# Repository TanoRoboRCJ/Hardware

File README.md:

# Hardware

ロボットのハードウェアについてのリポジトリです。主に基板を扱います。

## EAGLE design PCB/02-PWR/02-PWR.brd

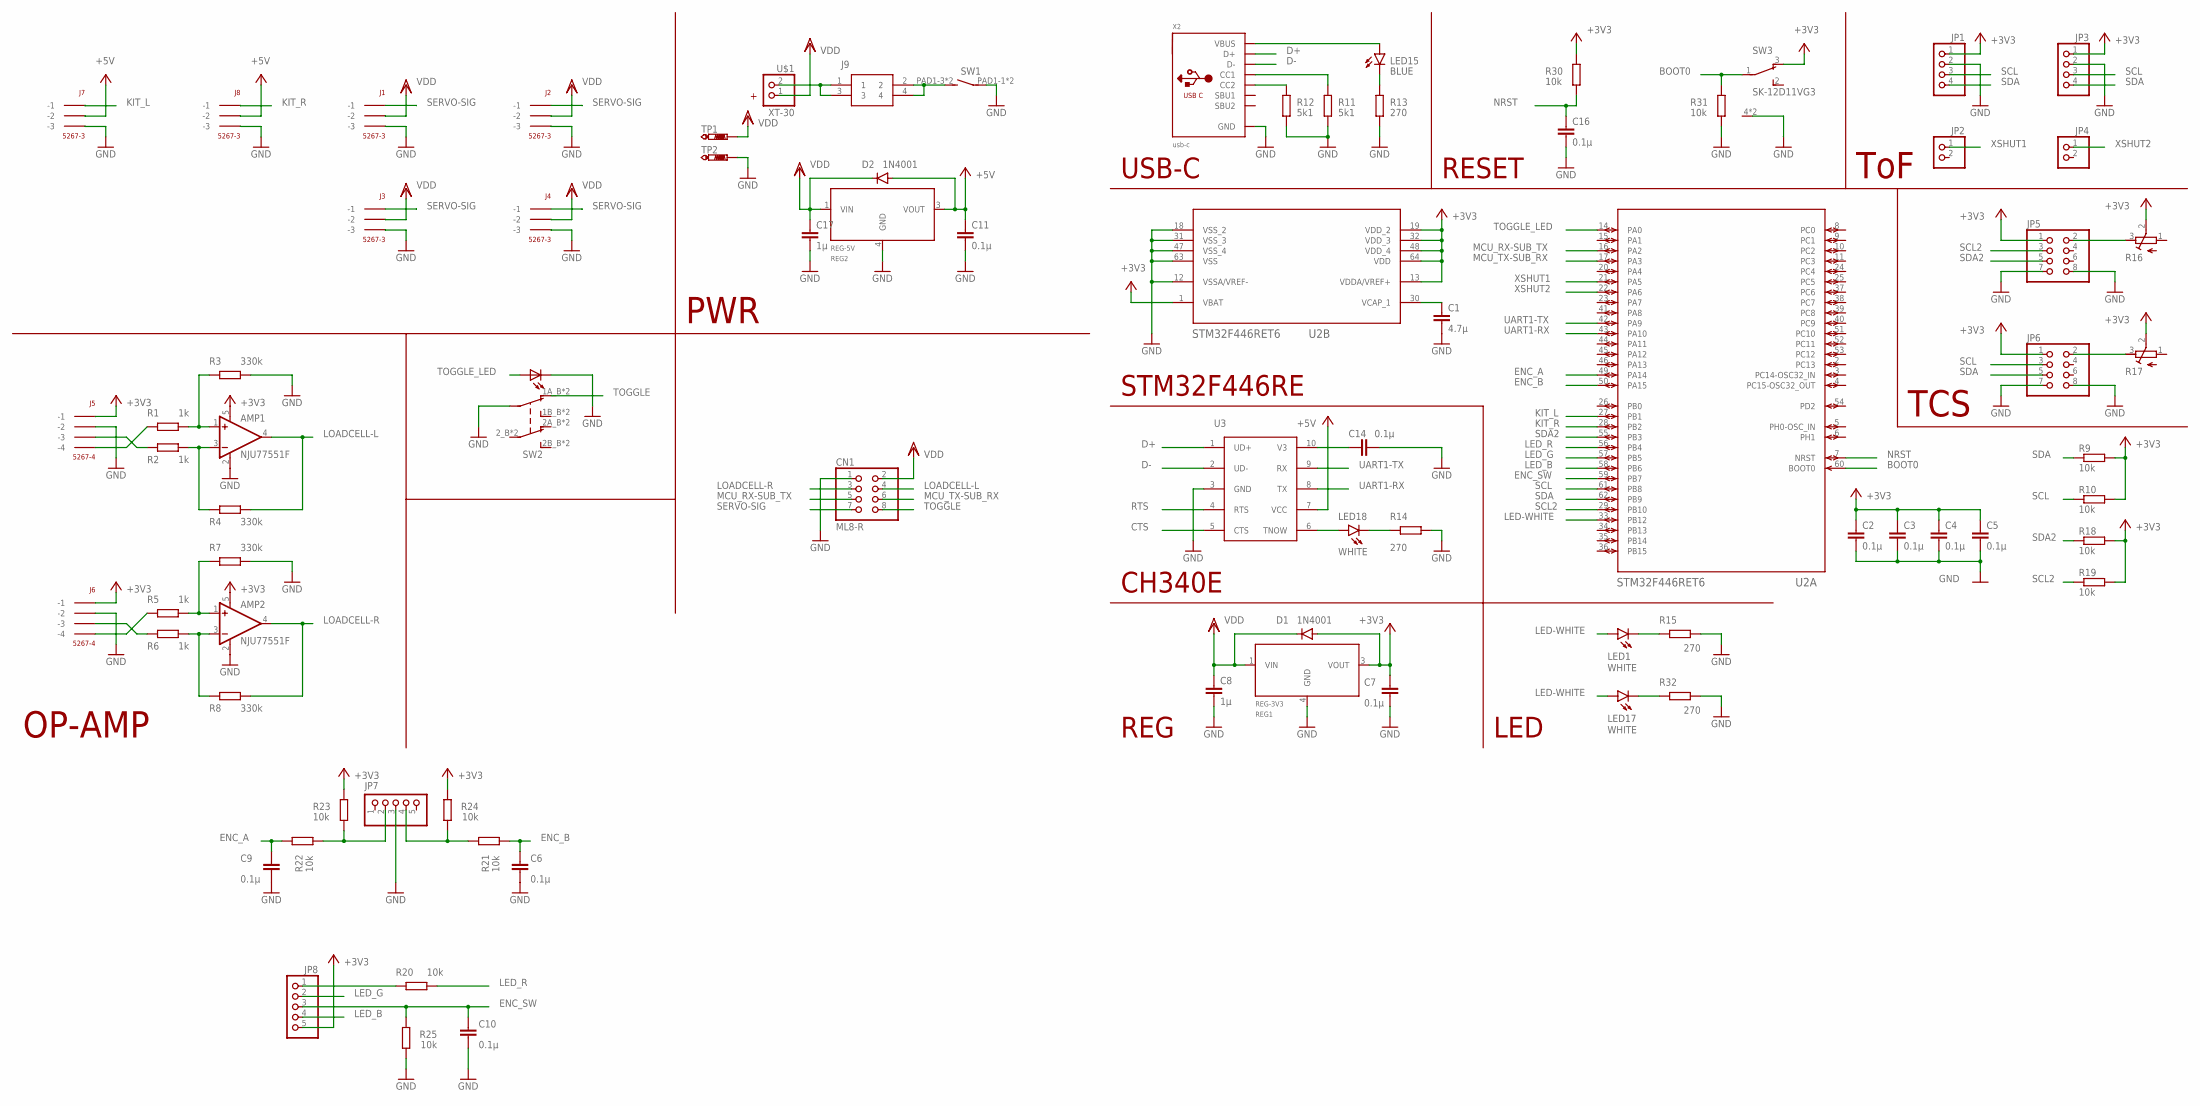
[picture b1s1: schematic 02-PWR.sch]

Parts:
AMP1, AMP2: NJU77551F; SOT23-5
C1: 4.7µ; C0603
C2, C3, C4, C5, C6, C7, C9, C10, C11, C14, C16: 0.1µ; C0603
C8, C17: 1µ; C0603
CN1: ML8-R; ML6
D1, D2: 1N4001; SMA-DO214AC
J1, J2, J3, J4, J7, J8: 5267-3
J5, J6: 5267-4
J9: 3557-2
JP1, JP3: PINHD-1X4; 1X04
JP2, JP4: PINHD-1X2; 1X02
JP5, JP6: PINHD-2X4; 2X04
JP7, JP8: PINHD-1X5; 1X05
LED1, LED17, LED18: WHITE; SML0603
LED15: BLUE; SML0603
R1, R2, R5, R6: 1k; R0805
R3, R4, R7, R8: 330k; R0805
R9, R10, R18, R19, R20, R21, R22, R23, R24, R25, R30, R31: 10k; R0402
R11, R12: 5k1; R0402
R13, R14, R15, R32: 270; R0402
R16, R17: R-TRIMM3339P; RTRIM3339P
REG1: REG-3V3; MYPARTS_D-PAK_TO252AA
REG2: REG-5V; MYPARTS_D-PAK_TO252AA
SW1: MYPARTS2_C01B02BKBK-EI
SW2: TL22
SW3: SK-12D11VG3
TP1, TP2: PTR1TP16R; TP16R
U2: STM32F446RET6; LQFP64-10X10MM
U3: CH340ESMD; MSOP10
U$1: XT-30
X2: usb-c; USB_C_CUSB31-CFM2AX-01-X

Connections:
+3V3: AMP1.5 (V+), AMP2.5 (V+), C2.1, C3.1, C4.1, C5.1, C7.1, D1.A, J5.P$1 (-1), J6.P$1 (-1), JP1.1, JP3.1, JP5.1, JP6.1, JP8.5, R9.2, R10.2, R16.2 (S), R17.2 (S), R18.2, R19.2, R23.1, R24.1, R30.1, REG1.3 (VOUT), SW3.3 (O), U2.1 (VBAT), U2.13 (VDDA/VREF+), U2.19 (VDD_2), U2.32 (VDD_3), U2.48 (VDD_4), U2.64 (VDD)
+5V: C11.1, D2.A, J7.P$2 (-2), J8.P$2 (-2), REG2.3 (VOUT), U3.7 (VCC)
BOOT0: R31.1, SW3.1, U2.60 (BOOT0)
CTS: U3.5 (CTS)
D+: U3.1 (UD+), X2.A6 (D+), X2.B6 (D+)
D-: U3.2 (UD-), X2.A7 (D-), X2.B7 (D-)
ENC_A: C9.1, R22.1, U2.49 (PA14)
ENC_B: C6.1, R21.2, U2.50 (PA15)
ENC_SW: C10.1, JP8.3, R25.1, U2.59 (PB7)
GND: AMP1.2 (V-), AMP2.2 (V-), C1.2, C2.2, C3.2, C4.2, C5.2, C6.2, C7.2, C8.2, C9.2, C10.2, C11.2, C14.2, C16.2, C17.2, CN1.1, J1.P$3 (-3), J2.P$3 (-3), J3.P$3 (-3), J4.P$3 (-3), J5.P$2 (-2), J6.P$2 (-2), J7.P$3 (-3), J8.P$3 (-3), JP1.2, JP3.2, JP5.7, JP5.8, JP6.7, JP6.8, JP7.3, R3.2, R7.2, R11.2, R12.2, R13.1, R14.1, R15.1, R25.2, R31.2, R32.1, REG1.4 (GND), REG2.4 (GND), SW1.PAD1-1, SW1.PAD1-2, SW2.1_B (1), SW2.1_T (1), SW2.L-_B (C), SW2.L-_T (C), SW3.4 (CASE), SW3.5 (CASE), TP2.TP, U2.12 (VSSA/VREF-), U2.18 (VSS_2), U2.31 (VSS_3), U2.47 (VSS_4), U2.63 (VSS), U3.3 (GND), X2.A1B12 (GND), X2.B1A12 (GND)
KIT_L: J7.P$1 (-1), U2.27 (PB1)
KIT_R: J8.P$1 (-1), U2.28 (PB2)
LED-WHITE: LED1.A, LED17.A, U2.33 (PB12)
LED_B: JP8.4, U2.58 (PB6)
LED_G: JP8.2, U2.57 (PB5)
LED_R: R20.2, U2.56 (PB4)
LOADCELL-L: AMP1.4 (OUT), CN1.4, R4.2
LOADCELL-R: AMP2.4 (OUT), CN1.3, R8.2
MCU_RX-SUB_TX: CN1.5, U2.16 (PA2)
MCU_TX-SUB_RX: CN1.6, U2.17 (PA3)
unnamed: J5.P$3 (-3), R2.1
unnamed: J5.P$4 (-4), R1.1
unnamed: AMP1.3 (-IN), R2.2, R4.1
unnamed: AMP1.1 (+IN), R1.2, R3.1
unnamed: J6.P$3 (-3), R6.1
unnamed: J6.P$4 (-4), R5.1
unnamed: AMP2.3 (-IN), R6.2, R8.1
unnamed: AMP2.1 (+IN), R5.2, R7.1
unnamed: J9.1, J9.3, U$1.2
unnamed: J9.2, J9.4, SW1.PAD1-3 (S), SW1.PAD1-4 (S)
unnamed: C14.1, U3.10 (V3)
unnamed: LED1.C, R15.2
unnamed: JP5.2, R16.3 (E)
unnamed: R11.1, X2.A5 (CC1)
unnamed: R12.1, X2.B5 (CC2)
unnamed: LED15.C, R13.2
unnamed: JP6.2, R17.3 (E)
unnamed: C1.1, U2.30 (VCAP_1)
unnamed: LED18.A, U3.6 (TNOW)
unnamed: LED18.C, R14.2
unnamed: JP7.4, R21.1, R24.2
unnamed: JP7.2, R22.2, R23.2
unnamed: JP8.1, R20.1
unnamed: LED17.C, R32.2
unnamed: LED15.A, X2.A4B9 (VBUS), X2.B4A9 (VBUS)
NRST: C16.1, R30.2, U2.7 (NRST)
RTS: U3.4 (RTS)
SCL: JP1.3, JP3.3, JP6.3, R10.1, U2.61 (PB8)
SCL2: JP5.3, R19.1, U2.29 (PB10)
SDA: JP1.4, JP3.4, JP6.5, R9.1, U2.62 (PB9)
SDA2: JP5.5, R18.1, U2.55 (PB3)
SERVO-SIG: CN1.7, J1.P$1 (-1), J2.P$1 (-1), J3.P$1 (-1), J4.P$1 (-1)
TOGGLE: CN1.8, SW2.1A_B (1A), SW2.1A_T (1A)
TOGGLE_LED: SW2.L+_B (A), SW2.L+_T (A), U2.14 (PA0)
UART1-RX: U2.43 (PA10), U3.8 (TX)
UART1-TX: U2.42 (PA9), U3.9 (RX)
VDD: C8.1, C17.1, CN1.2, D1.K (C), D2.K (C), J1.P$2 (-2), J2.P$2 (-2), J3.P$2 (-2), J4.P$2 (-2), REG1.1 (VIN), REG2.1 (VIN), TP1.TP, U$1.1
XSHUT1: JP2.1, U2.21 (PA5)
XSHUT2: JP4.1, U2.22 (PA6)

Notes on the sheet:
PWR
ToF
OP-AMP
STM32F446RE
REG
CH340E
USB-C
RESET
LED
TCS

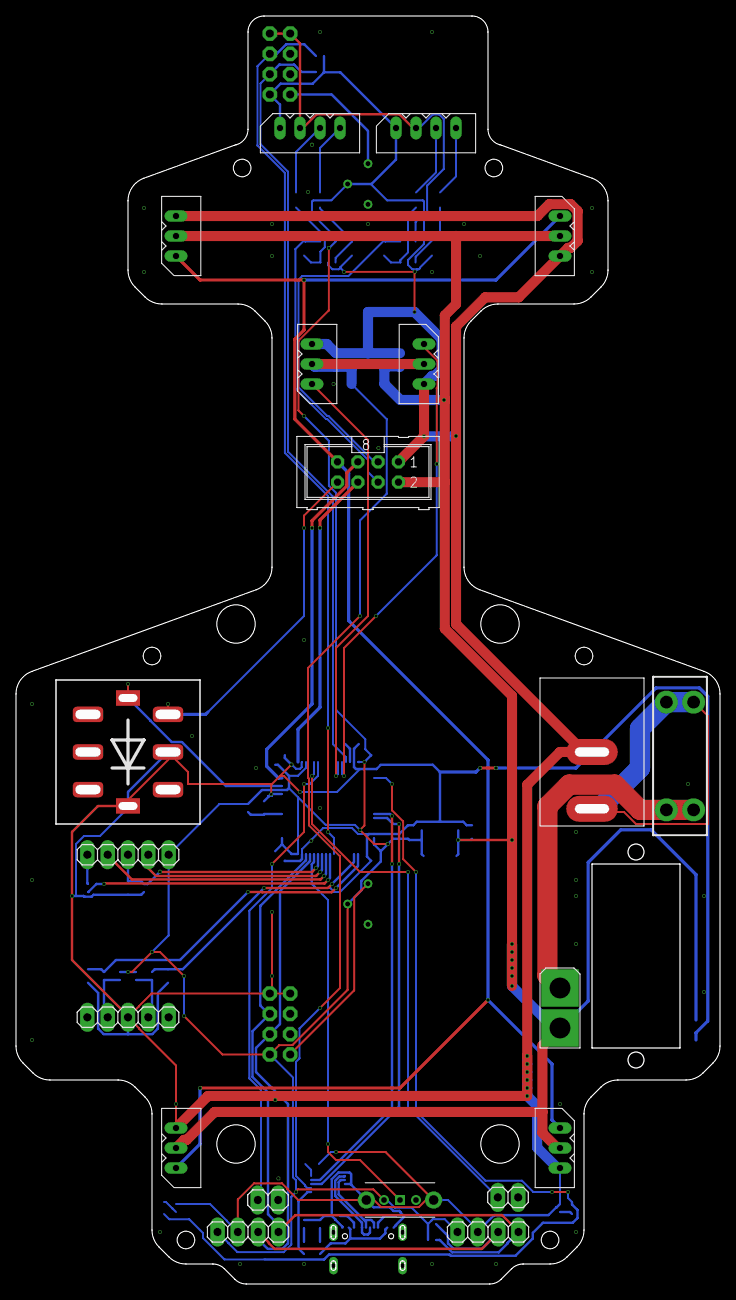
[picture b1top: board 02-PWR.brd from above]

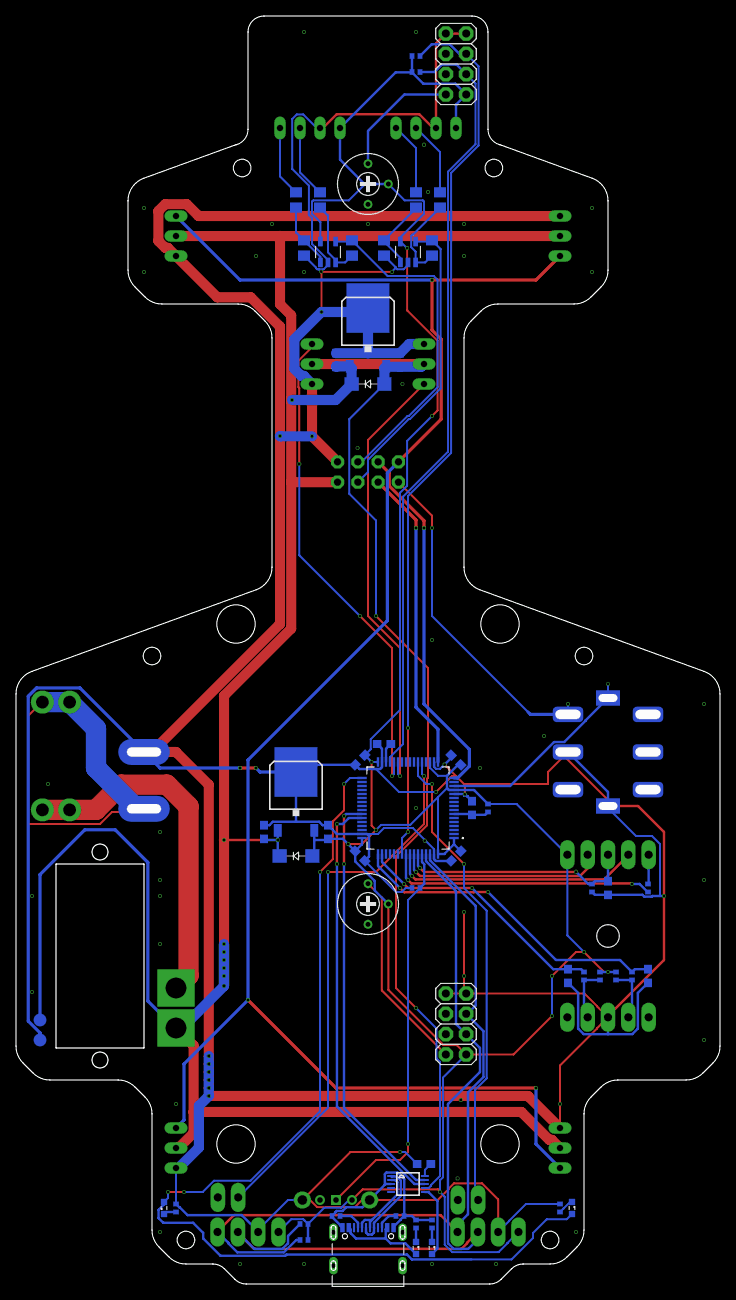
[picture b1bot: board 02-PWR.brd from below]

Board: 2 copper layers, 88.0 x 158.5 mm, 79 parts (59 on the bottom side), 57 nets.

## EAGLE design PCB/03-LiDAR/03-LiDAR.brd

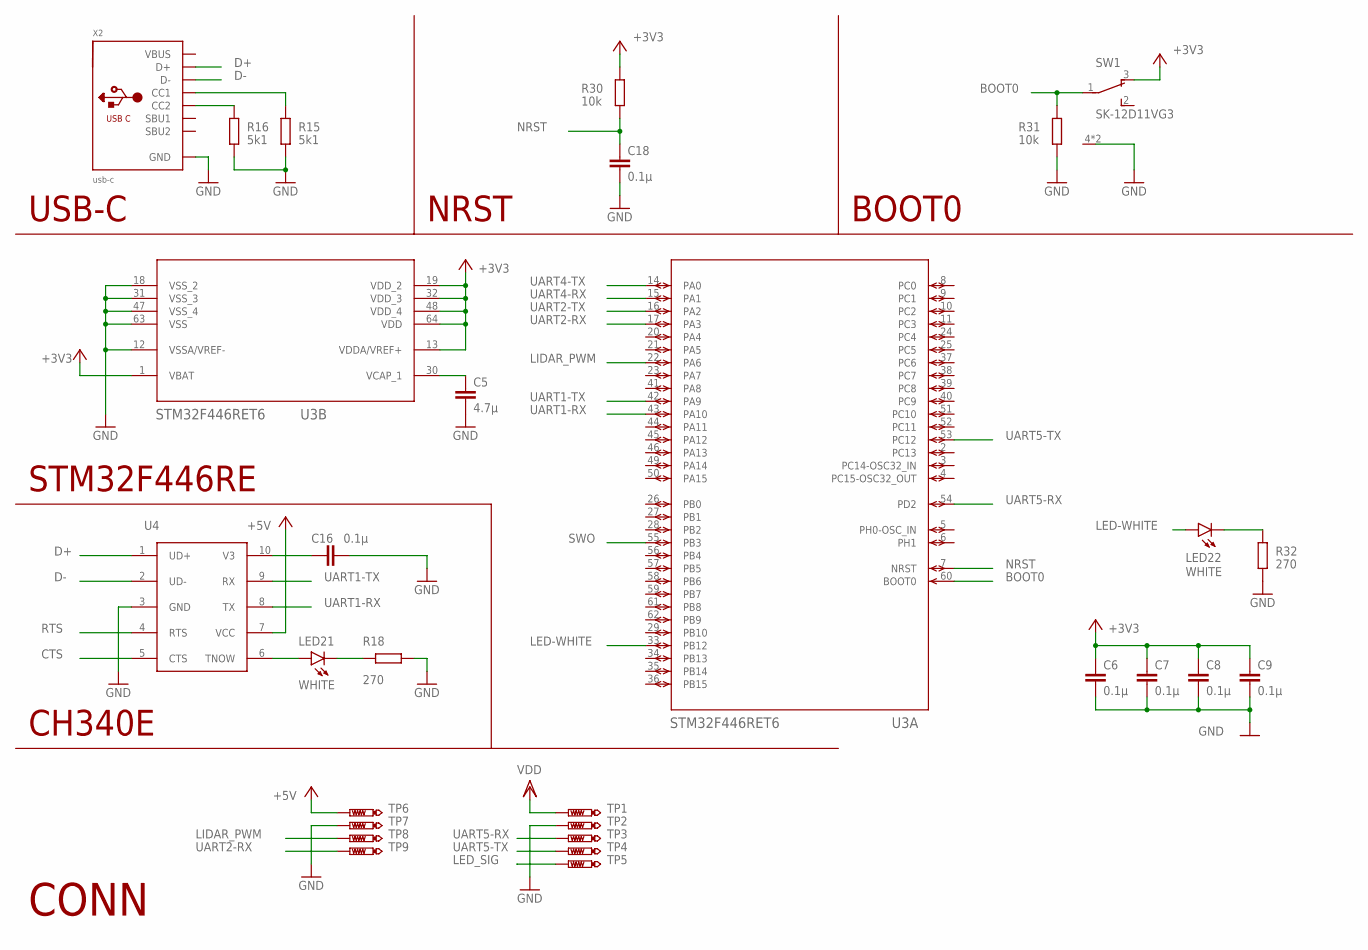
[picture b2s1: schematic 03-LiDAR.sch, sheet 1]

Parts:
C5: 4.7µ; C0603
C6, C7, C8, C9, C16, C18: 0.1µ; C0603
LED21, LED22: WHITE; SML0603
R15, R16: 5k1; R0402
R18, R32: 270; R0402
R30, R31: 10k; R0402
SW1: SK-12D11VG3
TP1, TP3, TP4, TP5, TP6, TP8, TP9: PTR1TP10R; TP10R
TP2, TP7: PTR1TP10SQ; TP10SQ
U3: STM32F446RET6; LQFP64-10X10MM
U4: CH340ESMD; MSOP10
X2: usb-c; USB_C_CUSB31-CFM2AX-01-X

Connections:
+3V3: C6.1, C7.1, C8.1, C9.1, R30.1, SW1.3 (O), U3.1 (VBAT), U3.13 (VDDA/VREF+), U3.19 (VDD_2), U3.32 (VDD_3), U3.48 (VDD_4), U3.64 (VDD); also elsewhere on the board
+5V: TP6.TP, U4.7 (VCC); also elsewhere on the board
BOOT0: R31.1, SW1.1, U3.60 (BOOT0)
CTS: U4.5 (CTS)
D+: U4.1 (UD+), X2.A6 (D+), X2.B6 (D+)
D-: U4.2 (UD-), X2.A7 (D-), X2.B7 (D-)
GND: C5.2, C6.2, C7.2, C8.2, C9.2, C16.2, C18.2, R15.2, R16.2, R18.1, R31.2, R32.1, SW1.4 (CASE), SW1.5 (CASE), TP2.TP, TP7.TP, U3.12 (VSSA/VREF-), U3.18 (VSS_2), U3.31 (VSS_3), U3.47 (VSS_4), U3.63 (VSS), U4.3 (GND), X2.A1B12 (GND), X2.B1A12 (GND); also elsewhere on the board
LED-WHITE: LED22.A, U3.33 (PB12)
LED_SIG: TP5.TP; also elsewhere on the board
LIDAR_PWM: TP8.TP, U3.22 (PA6)
unnamed: R15.1, X2.A5 (CC1)
unnamed: R16.1, X2.B5 (CC2)
unnamed: C5.1, U3.30 (VCAP_1)
unnamed: C16.1, U4.10 (V3)
unnamed: LED21.A, U4.6 (TNOW)
unnamed: LED21.C, R18.2
unnamed: LED22.C, R32.2
NRST: C18.1, R30.2, U3.7 (NRST)
RTS: U4.4 (RTS)
SWO: U3.55 (PB3)
UART1-RX: U3.43 (PA10), U4.8 (TX)
UART1-TX: U3.42 (PA9), U4.9 (RX)
UART2-RX: TP9.TP, U3.17 (PA3)
UART2-TX: U3.16 (PA2)
UART4-RX: U3.15 (PA1); also elsewhere on the board
UART4-TX: U3.14 (PA0)
UART5-RX: TP3.TP, U3.54 (PD2); also elsewhere on the board
UART5-TX: TP4.TP, U3.53 (PC12)
VBUS: X2.A4B9 (VBUS), X2.B4A9 (VBUS)
VDD: TP1.TP; also elsewhere on the board

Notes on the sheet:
CONN
STM32F446RE
CH340E
USB-C
BOOT0
NRST

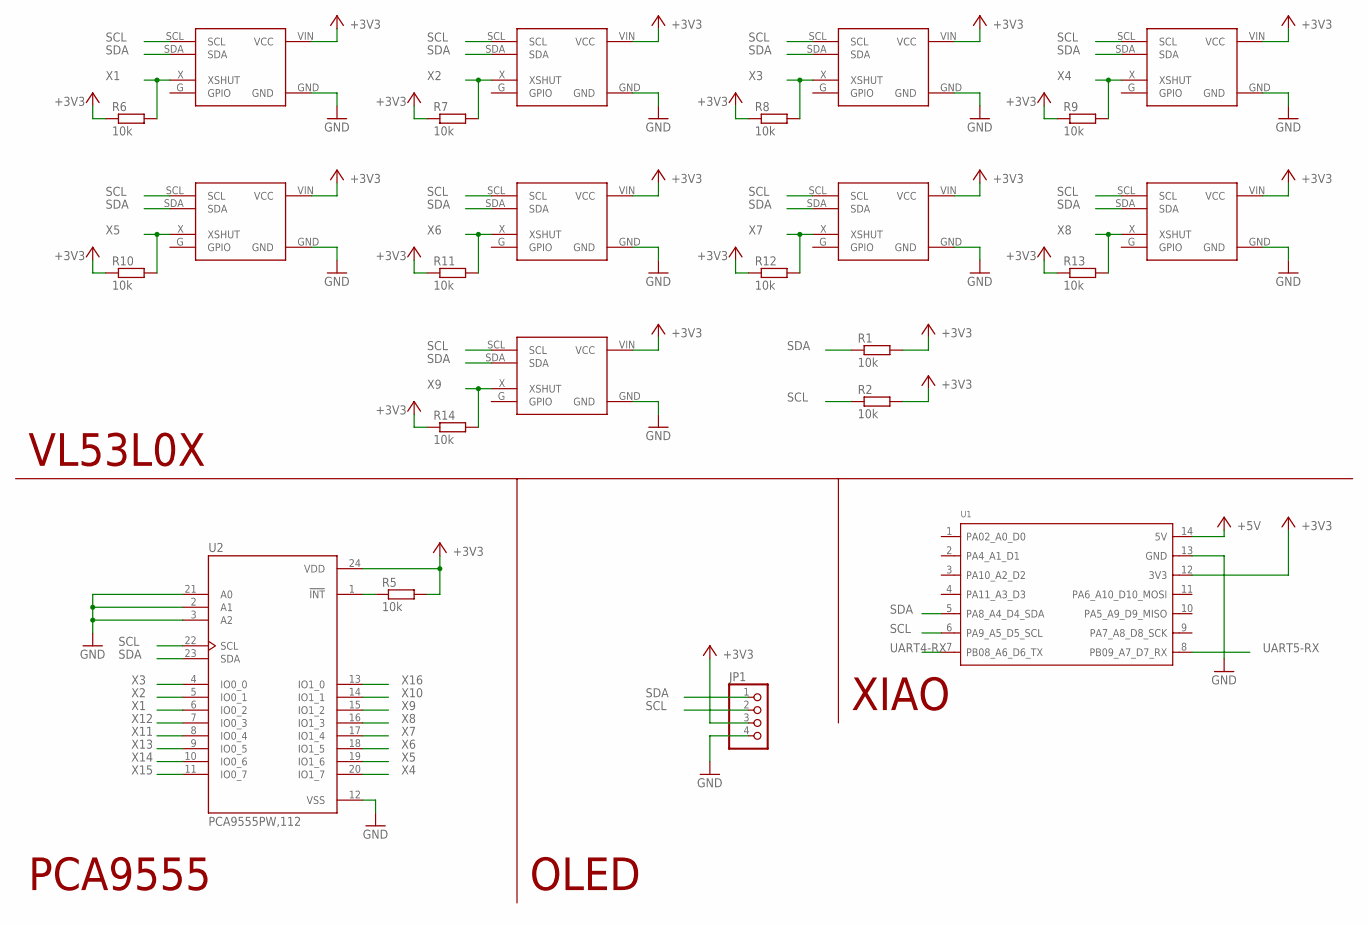
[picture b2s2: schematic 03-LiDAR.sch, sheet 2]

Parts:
JP1: PINHD-1X4; 1X04
R1, R2, R5, R6, R7, R8, R9, R10, R11, R12, R13, R14: 10k; R0402
U1: MOUDLE-SEEEDUINO-XIAO; MOUDLE14P-2.54-21X17.8MM
U2: PCA9555PW,112; SOP65P640X110-24N
VL1, VL2, VL3, VL4, VL5, VL6, VL7, VL8, VL9: VL53L0X; 1X04

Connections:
+3V3: JP1.3, R1.2, R2.2, R5.2, R6.1, R7.1, R8.1, R9.1, R10.1, R11.1, R12.1, R13.1, R14.1, U1.12 (3V3), U2.24 (VDD), VL1.VIN (VCC), VL2.VIN (VCC), VL3.VIN (VCC), VL4.VIN (VCC), VL5.VIN (VCC), VL6.VIN (VCC), VL7.VIN (VCC), VL8.VIN (VCC), VL9.VIN (VCC); also elsewhere on the board
+5V: U1.14 (5V); also elsewhere on the board
GND: JP1.4, U1.13 (GND), U2.2 (A1), U2.3 (A2), U2.12 (VSS), U2.21 (A0), VL1.GND, VL2.GND, VL3.GND, VL4.GND, VL5.GND, VL6.GND, VL7.GND, VL8.GND, VL9.GND; also elsewhere on the board
unnamed: R5.1, U2.1 (!INT)
SCL: JP1.2, R2.1, U1.6 (PA9_A5_D5_SCL), U2.22 (SCL), VL1.SCL, VL2.SCL, VL3.SCL, VL4.SCL, VL5.SCL, VL6.SCL, VL7.SCL, VL8.SCL, VL9.SCL
SDA: JP1.1, R1.1, U1.5 (PA8_A4_D4_SDA), U2.23 (SDA), VL1.SDA, VL2.SDA, VL3.SDA, VL4.SDA, VL5.SDA, VL6.SDA, VL7.SDA, VL8.SDA, VL9.SDA
UART4-RX: U1.7 (PB08_A6_D6_TX); also elsewhere on the board
UART5-RX: U1.8 (PB09_A7_D7_RX); also elsewhere on the board
X1: R6.2, U2.6 (IO0_2), VL1.X (XSHUT)
X2: R7.2, U2.5 (IO0_1), VL2.X (XSHUT)
X3: R8.2, U2.4 (IO0_0), VL3.X (XSHUT)
X4: R9.2, U2.20 (IO1_7), VL4.X (XSHUT)
X5: R10.2, U2.19 (IO1_6), VL5.X (XSHUT)
X6: R11.2, U2.18 (IO1_5), VL6.X (XSHUT)
X7: R12.2, U2.17 (IO1_4), VL7.X (XSHUT)
X8: R13.2, U2.16 (IO1_3), VL8.X (XSHUT)
X9: R14.2, U2.15 (IO1_2), VL9.X (XSHUT)
X10: U2.14 (IO1_1)
X11: U2.8 (IO0_4)
X12: U2.7 (IO0_3)
X13: U2.9 (IO0_5)
X14: U2.10 (IO0_6)
X15: U2.11 (IO0_7)
X16: U2.13 (IO1_0)

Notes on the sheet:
VL53L0X
XIAO
PCA9555
OLED

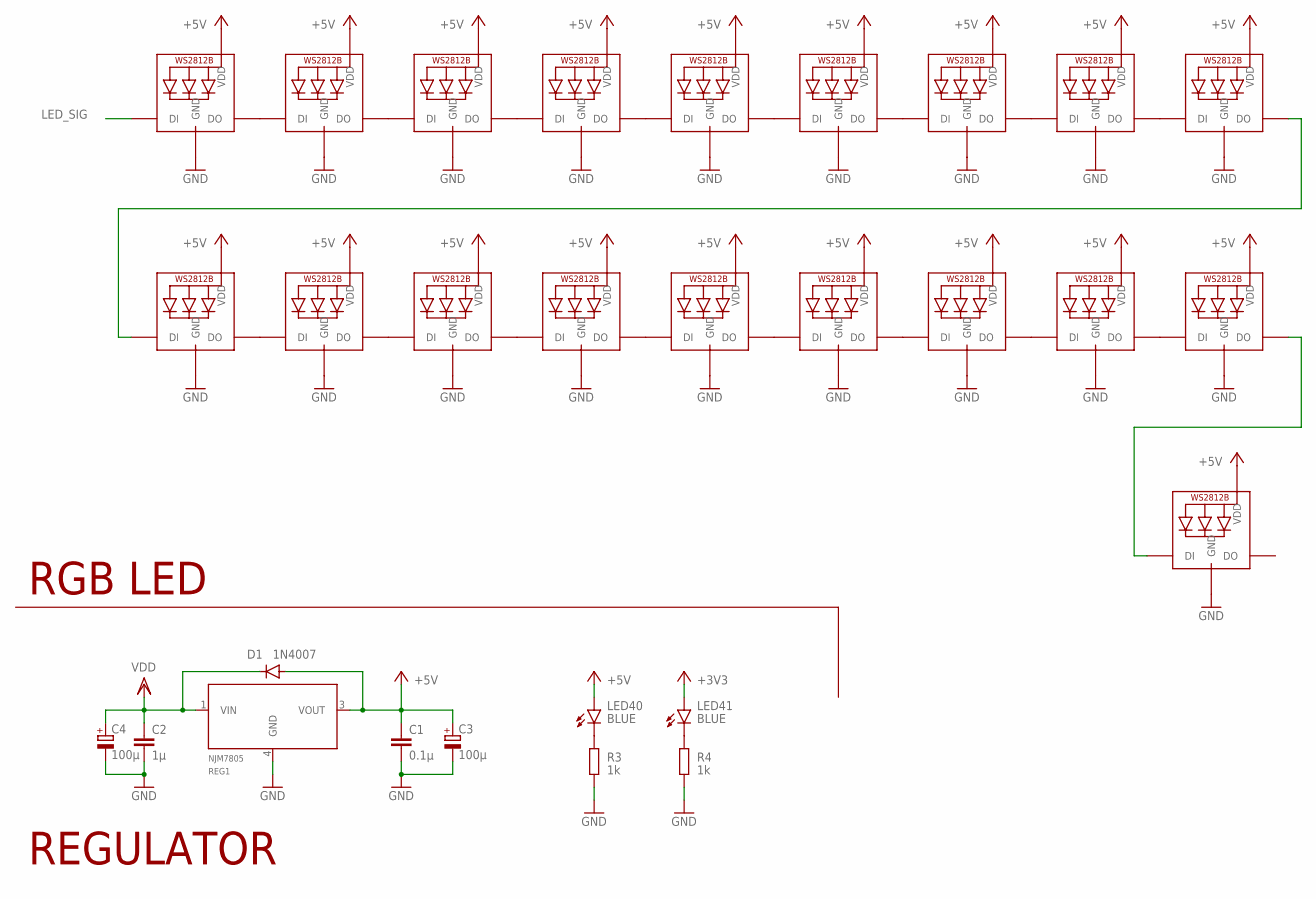
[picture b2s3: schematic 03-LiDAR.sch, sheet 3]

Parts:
C1: 0.1μ; C0402
C2: 1μ; C0402
C3, C4: 100μ; 153CLV-0505
D1: 1N4007; SMA-DO214AC
LED1, LED2, LED3, LED4, LED5, LED6, LED7, LED8, LED9, LED10, LED11, LED12, LED13, LED14, LED15, LED16, LED17, LED18, LED19: WS2812B_5050N; WS2812B-NARROW
LED40, LED41: BLUE; SML0603
R3, R4: 1k; R0402
REG1: NJM7805; MYPARTS_D-PAK_TO252AA

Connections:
+3V3: LED41.A; also elsewhere on the board
+5V: C1.1, C3.+, D1.A, LED1.1-VDD (VDD), LED2.1-VDD (VDD), LED3.1-VDD (VDD), LED4.1-VDD (VDD), LED5.1-VDD (VDD), LED6.1-VDD (VDD), LED7.1-VDD (VDD), LED8.1-VDD (VDD), LED9.1-VDD (VDD), LED10.1-VDD (VDD), LED11.1-VDD (VDD), LED12.1-VDD (VDD), LED13.1-VDD (VDD), LED14.1-VDD (VDD), LED15.1-VDD (VDD), LED16.1-VDD (VDD), LED17.1-VDD (VDD), LED18.1-VDD (VDD), LED19.1-VDD (VDD), LED40.A, REG1.3 (VOUT); also elsewhere on the board
GND: C1.2, C2.2, C3.-, C4.-, LED1.3-GND (GND), LED2.3-GND (GND), LED3.3-GND (GND), LED4.3-GND (GND), LED5.3-GND (GND), LED6.3-GND (GND), LED7.3-GND (GND), LED8.3-GND (GND), LED9.3-GND (GND), LED10.3-GND (GND), LED11.3-GND (GND), LED12.3-GND (GND), LED13.3-GND (GND), LED14.3-GND (GND), LED15.3-GND (GND), LED16.3-GND (GND), LED17.3-GND (GND), LED18.3-GND (GND), LED19.3-GND (GND), R3.2, R4.2, REG1.4 (GND); also elsewhere on the board
LED_SIG: LED1.4-DIN (DI); also elsewhere on the board
unnamed: LED1.2-DOUT (DO), LED2.4-DIN (DI)
unnamed: LED2.2-DOUT (DO), LED3.4-DIN (DI)
unnamed: LED3.2-DOUT (DO), LED4.4-DIN (DI)
unnamed: LED4.2-DOUT (DO), LED5.4-DIN (DI)
unnamed: LED5.2-DOUT (DO), LED6.4-DIN (DI)
unnamed: LED6.2-DOUT (DO), LED7.4-DIN (DI)
unnamed: LED7.2-DOUT (DO), LED8.4-DIN (DI)
unnamed: LED8.2-DOUT (DO), LED9.4-DIN (DI)
unnamed: LED10.2-DOUT (DO), LED11.4-DIN (DI)
unnamed: LED11.2-DOUT (DO), LED12.4-DIN (DI)
unnamed: LED12.2-DOUT (DO), LED13.4-DIN (DI)
unnamed: LED13.2-DOUT (DO), LED14.4-DIN (DI)
unnamed: LED14.2-DOUT (DO), LED15.4-DIN (DI)
unnamed: LED15.2-DOUT (DO), LED16.4-DIN (DI)
unnamed: LED16.2-DOUT (DO), LED17.4-DIN (DI)
unnamed: LED17.2-DOUT (DO), LED18.4-DIN (DI)
unnamed: LED40.C, R3.1
unnamed: LED41.C, R4.1
unnamed: LED9.2-DOUT (DO), LED10.4-DIN (DI)
unnamed: LED18.2-DOUT (DO), LED19.4-DIN (DI)
VDD: C2.1, C4.+, D1.K (C), REG1.1 (VIN); also elsewhere on the board

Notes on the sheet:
REGULATOR
RGB LED

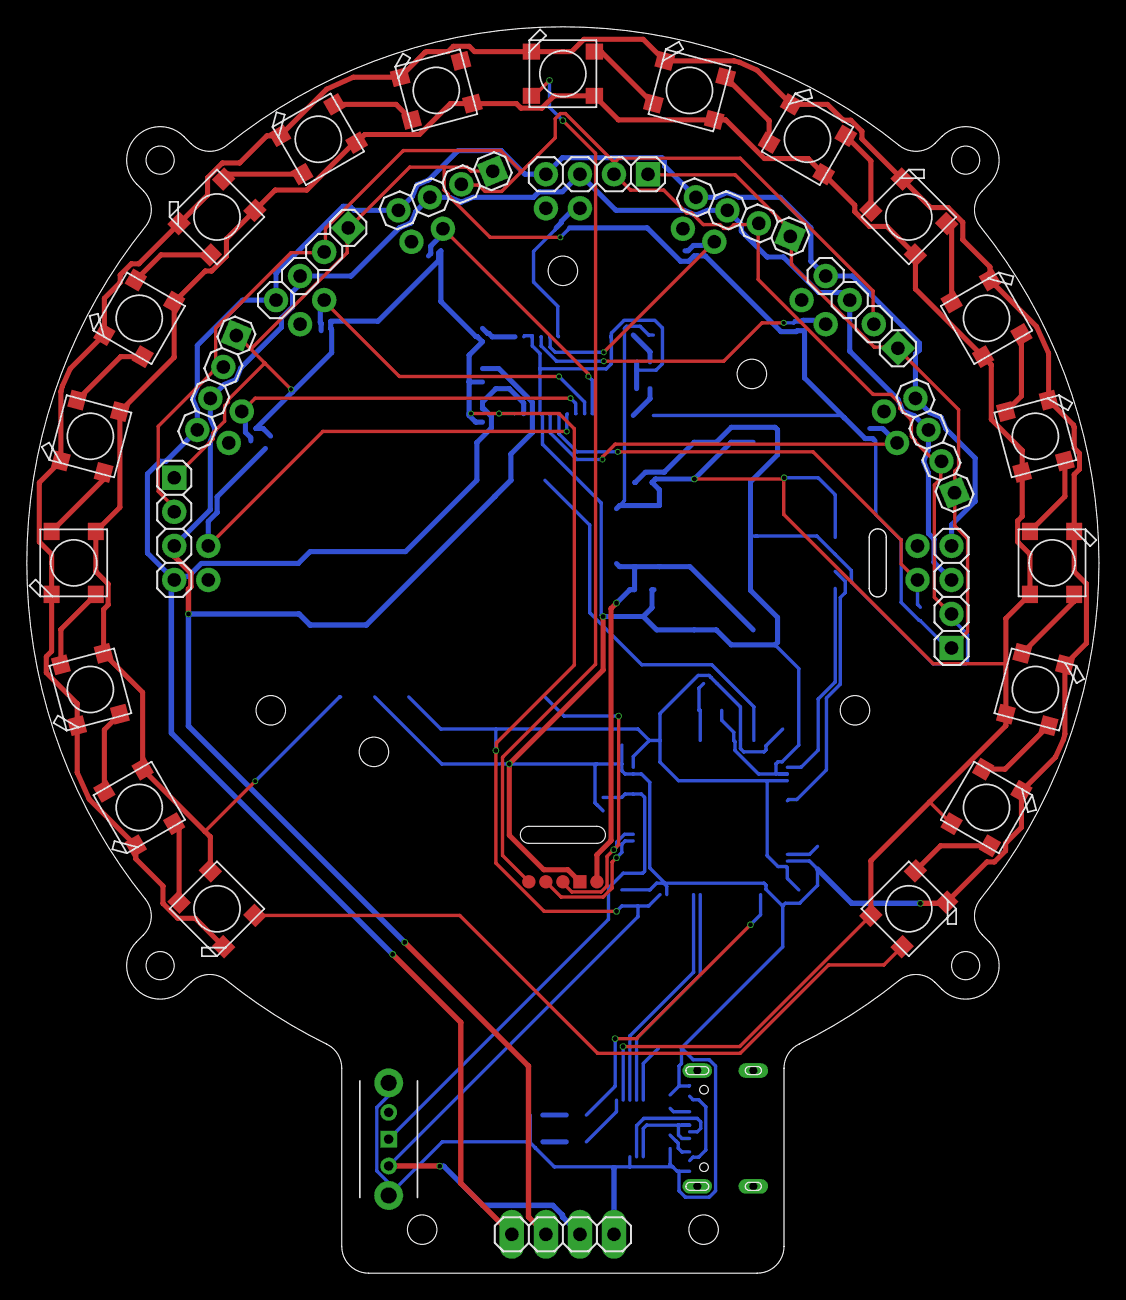
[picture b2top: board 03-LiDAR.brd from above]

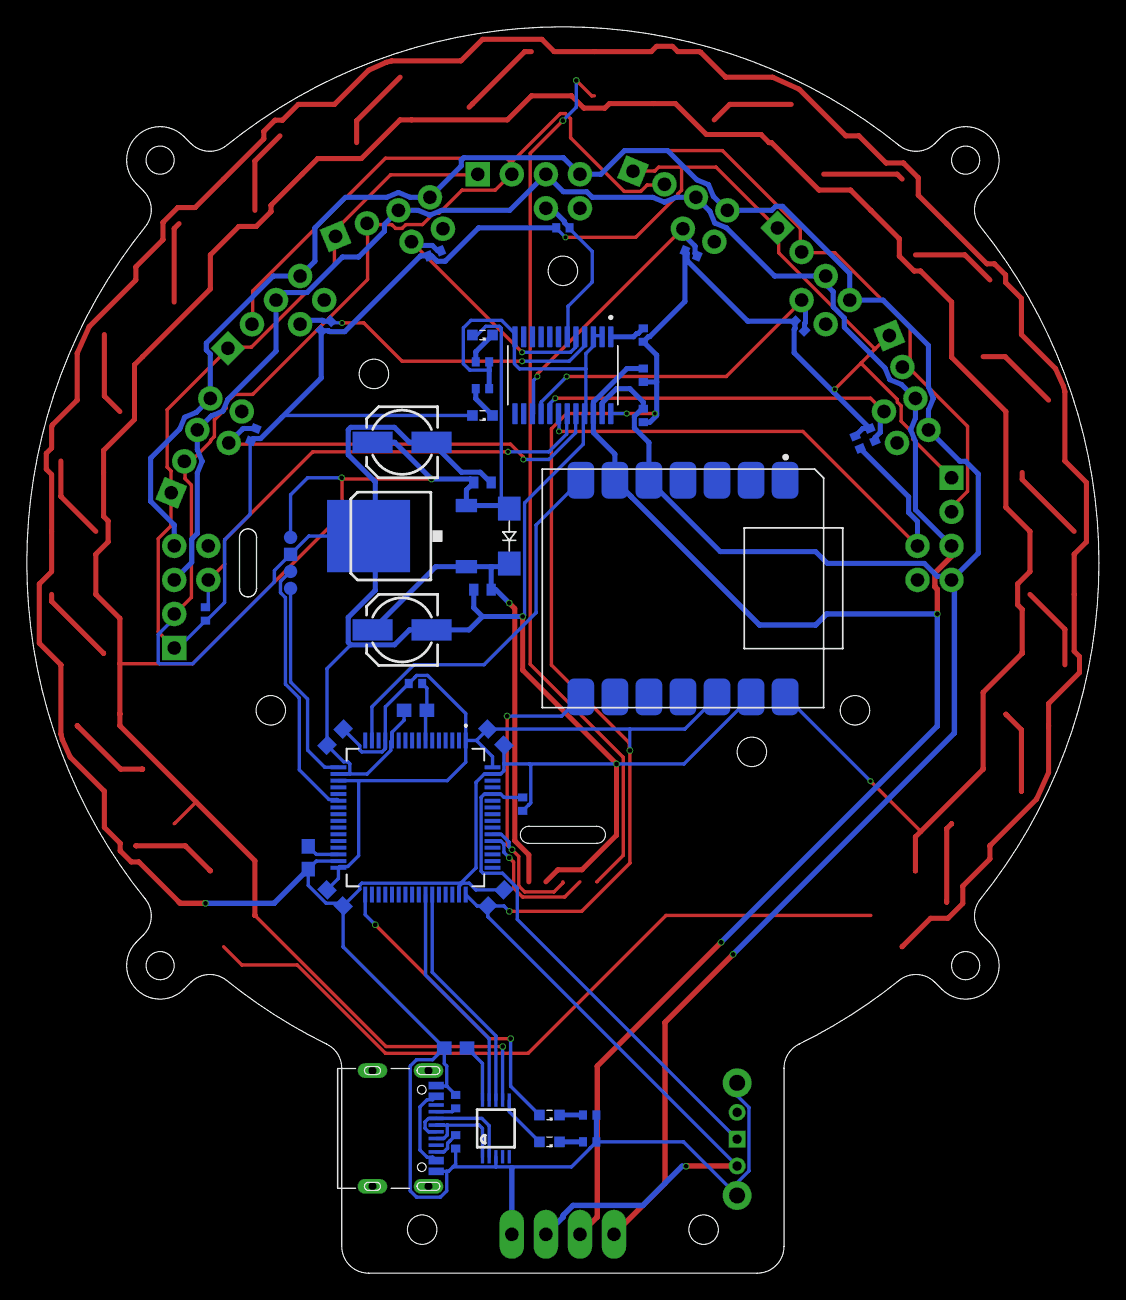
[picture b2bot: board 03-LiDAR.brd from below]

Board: 2 copper layers, 80.0 x 93.0 mm, 81 parts (46 on the bottom side), 57 nets.

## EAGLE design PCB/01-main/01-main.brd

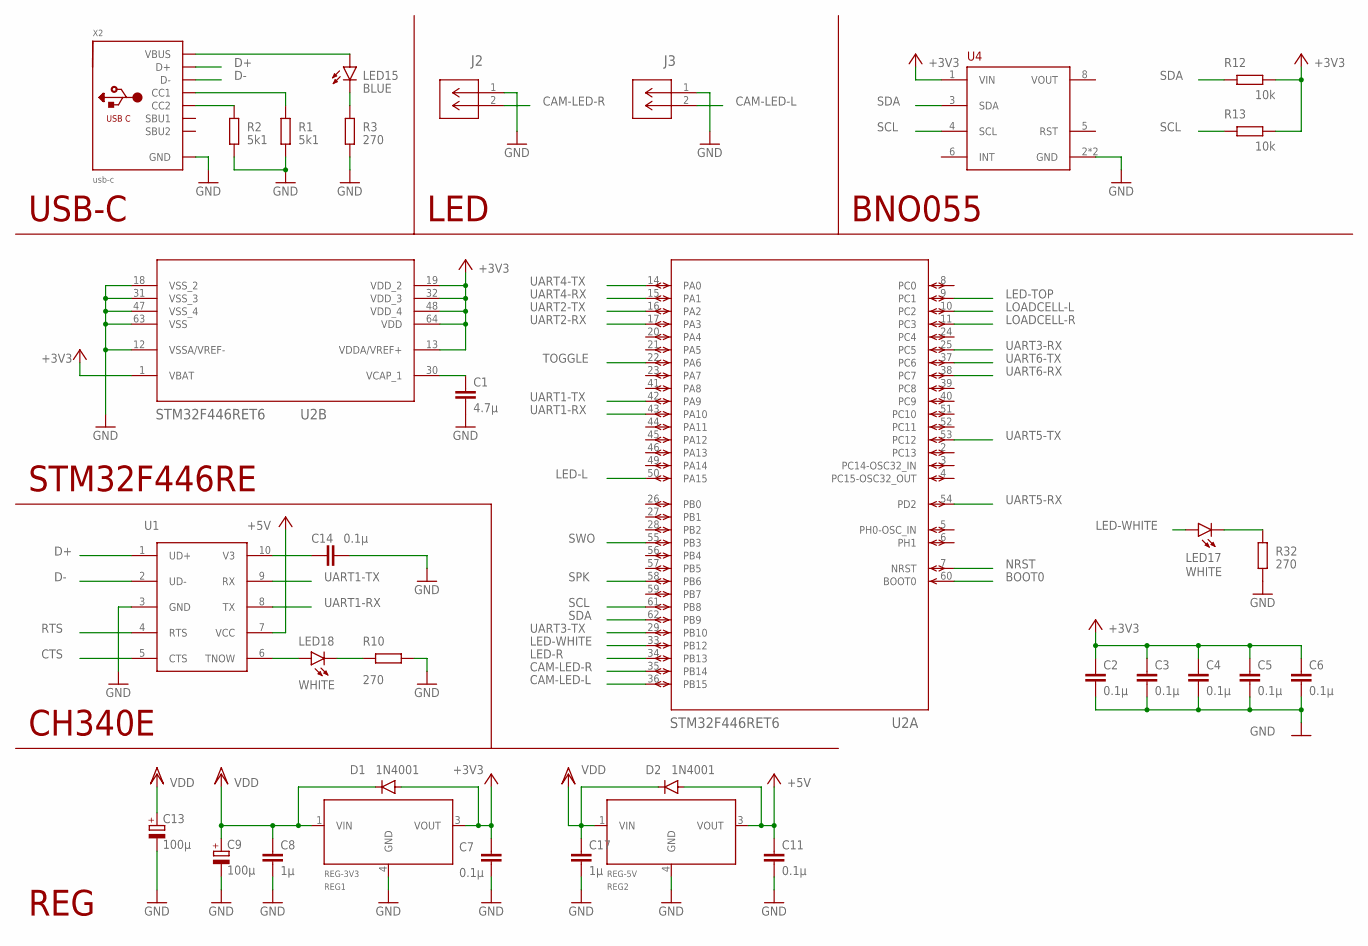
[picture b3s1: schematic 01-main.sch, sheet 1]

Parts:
C1: 4.7µ; C0603
C2, C3, C4, C5, C6, C7, C11, C14: 0.1µ; C0603
C8, C17: 1µ; C0603
C9, C13: 100μ; 153CLV-0505
D1, D2: 1N4001; SMA-DO214AC
J2, J3: 22057025; CON_22057025_MOL
LED15: BLUE; SML0603
LED17, LED18: WHITE; SML0603
R1, R2: 5k1; R0402
R3, R10, R32: 270; R0402
R12, R13: 10k; R0402
REG1: REG-3V3; MYPARTS_D-PAK_TO252AA
REG2: REG-5V; MYPARTS_D-PAK_TO252AA
U1: CH340ESMD; MSOP10
U2: STM32F446RET6; LQFP64-10X10MM
U4: BNO055; SOCKET-08
X2: usb-c; USB_C_CUSB31-CFM2AX-01-X

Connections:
+3V3: C2.1, C3.1, C4.1, C5.1, C6.1, C7.1, D1.A, R12.1, R13.1, REG1.3 (VOUT), U2.1 (VBAT), U2.13 (VDDA/VREF+), U2.19 (VDD_2), U2.32 (VDD_3), U2.48 (VDD_4), U2.64 (VDD), U4.1 (VIN); also elsewhere on the board
+5V: C11.1, D2.A, REG2.3 (VOUT), U1.7 (VCC); also elsewhere on the board
BOOT0: U2.60 (BOOT0); also elsewhere on the board
CAM-LED-L: J3.2, U2.36 (PB15)
CAM-LED-R: J2.2, U2.35 (PB14)
CTS: U1.5 (CTS)
D+: U1.1 (UD+), X2.A6 (D+), X2.B6 (D+)
D-: U1.2 (UD-), X2.A7 (D-), X2.B7 (D-)
GND: C1.2, C2.2, C3.2, C4.2, C5.2, C6.2, C7.2, C8.2, C9.-, C11.2, C13.-, C14.2, C17.2, J2.1, J3.1, R1.2, R2.2, R3.1, R10.1, R32.1, REG1.4 (GND), REG2.4 (GND), U1.3 (GND), U2.12 (VSSA/VREF-), U2.18 (VSS_2), U2.31 (VSS_3), U2.47 (VSS_4), U2.63 (VSS), U4.2 (GND), U4.7 (GND), X2.A1B12 (GND), X2.B1A12 (GND); also elsewhere on the board
LED-L: U2.50 (PA15); also elsewhere on the board
LED-R: U2.34 (PB13); also elsewhere on the board
LED-TOP: U2.9 (PC1); also elsewhere on the board
LED-WHITE: LED17.A, U2.33 (PB12)
LOADCELL-L: U2.10 (PC2); also elsewhere on the board
LOADCELL-R: U2.11 (PC3); also elsewhere on the board
unnamed: C14.1, U1.10 (V3)
unnamed: R1.1, X2.A5 (CC1)
unnamed: R2.1, X2.B5 (CC2)
unnamed: LED15.C, R3.2
unnamed: C1.1, U2.30 (VCAP_1)
unnamed: LED18.A, U1.6 (TNOW)
unnamed: LED18.C, R10.2
unnamed: LED17.C, R32.2
unnamed: LED15.A, X2.A4B9 (VBUS), X2.B4A9 (VBUS)
NRST: U2.7 (NRST); also elsewhere on the board
RTS: U1.4 (RTS)
SCL: R13.2, U2.61 (PB8), U4.4 (SCL)
SDA: R12.2, U2.62 (PB9), U4.3 (SDA)
SPK: U2.58 (PB6); also elsewhere on the board
SWO: U2.55 (PB3)
TOGGLE: U2.22 (PA6); also elsewhere on the board
UART1-RX: U1.8 (TX), U2.43 (PA10)
UART1-TX: U1.9 (RX), U2.42 (PA9); also elsewhere on the board
UART2-RX: U2.17 (PA3); also elsewhere on the board
UART2-TX: U2.16 (PA2); also elsewhere on the board
UART3-RX: U2.25 (PC5); also elsewhere on the board
UART3-TX: U2.29 (PB10); also elsewhere on the board
UART4-RX: U2.15 (PA1); also elsewhere on the board
UART4-TX: U2.14 (PA0); also elsewhere on the board
UART5-RX: U2.54 (PD2); also elsewhere on the board
UART5-TX: U2.53 (PC12); also elsewhere on the board
UART6-RX: U2.38 (PC7); also elsewhere on the board
UART6-TX: U2.37 (PC6); also elsewhere on the board
VDD: C8.1, C9.+, C13.+, C17.1, D1.K (C), D2.K (C), REG1.1 (VIN), REG2.1 (VIN); also elsewhere on the board
VOUT: U4.8 (VOUT)

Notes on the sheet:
STM32F446RE
REG
CH340E
USB-C
BNO055
LED

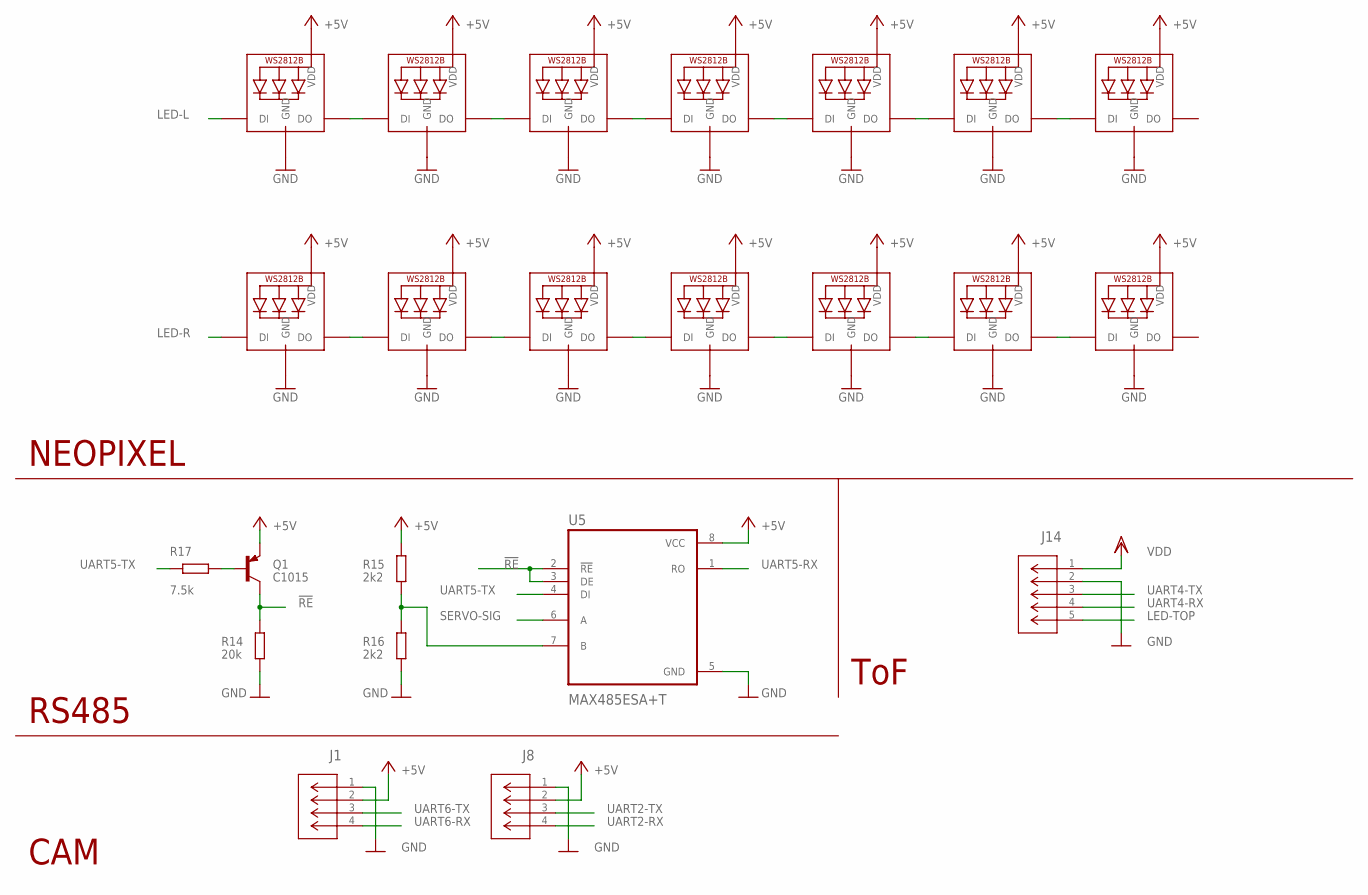
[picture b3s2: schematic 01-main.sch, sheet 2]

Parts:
J1, J8: 22057045; CON_22057045_MOL
J14: 22057055; CON_22057055_MOL
LED1, LED2, LED3, LED4, LED5, LED6, LED7, LED8, LED9, LED10, LED11, LED12, LED13, LED14: WS2812B_2020
Q1: C1015; SOT23
R14: 20k; R0402
R15, R16: 2k2; R0402
R17: 7.5k; R0402
U5: MAX485ESA+T; SOIC127P600X175-8N

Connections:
!RE: Q1.3 (C), R14.1, U5.2 (!RE), U5.3 (DE)
+5V: J1.2, J8.2, LED1.4 (VDD), LED2.4 (VDD), LED3.4 (VDD), LED4.4 (VDD), LED5.4 (VDD), LED6.4 (VDD), LED7.4 (VDD), LED8.4 (VDD), LED9.4 (VDD), LED10.4 (VDD), LED11.4 (VDD), LED12.4 (VDD), LED13.4 (VDD), LED14.4 (VDD), Q1.2 (E), R15.1, U5.8 (VCC); also elsewhere on the board
GND: J1.1, J8.1, J14.2, LED1.2 (GND), LED2.2 (GND), LED3.2 (GND), LED4.2 (GND), LED5.2 (GND), LED6.2 (GND), LED7.2 (GND), LED8.2 (GND), LED9.2 (GND), LED10.2 (GND), LED11.2 (GND), LED12.2 (GND), LED13.2 (GND), LED14.2 (GND), R14.2, R16.2, U5.5 (GND); also elsewhere on the board
LED-L: LED1.3 (DI); also elsewhere on the board
LED-R: LED8.3 (DI); also elsewhere on the board
LED-TOP: J14.5; also elsewhere on the board
unnamed: LED1.1 (DO), LED2.3 (DI)
unnamed: LED2.1 (DO), LED3.3 (DI)
unnamed: LED3.1 (DO), LED4.3 (DI)
unnamed: LED4.1 (DO), LED5.3 (DI)
unnamed: LED5.1 (DO), LED6.3 (DI)
unnamed: LED6.1 (DO), LED7.3 (DI)
unnamed: LED8.1 (DO), LED9.3 (DI)
unnamed: LED9.1 (DO), LED10.3 (DI)
unnamed: LED10.1 (DO), LED11.3 (DI)
unnamed: LED11.1 (DO), LED12.3 (DI)
unnamed: LED12.1 (DO), LED13.3 (DI)
unnamed: LED13.1 (DO), LED14.3 (DI)
unnamed: Q1.1 (B), R17.1
unnamed: R15.2, R16.1, U5.7 (B)
SERVO-SIG: U5.6 (A); also elsewhere on the board
UART2-RX: J8.4; also elsewhere on the board
UART2-TX: J8.3; also elsewhere on the board
UART4-RX: J14.4; also elsewhere on the board
UART4-TX: J14.3; also elsewhere on the board
UART5-RX: U5.1 (RO); also elsewhere on the board
UART5-TX: R17.2, U5.4 (DI); also elsewhere on the board
UART6-RX: J1.4; also elsewhere on the board
UART6-TX: J1.3; also elsewhere on the board
VDD: J14.1; also elsewhere on the board

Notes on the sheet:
NEOPIXEL
ToF
CAM
RS485

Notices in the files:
parts and their libraries:
COPYRIGHT: Copyright (C) 2022 Ultra Librarian. All rights reserved.
